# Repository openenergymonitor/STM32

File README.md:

# STM32 Energy Monitoring

The STM32 platform is a family of microcontrollers based on the Arm Cortex M processor, offering among many powerful features, plenty of 12-bit analog inputs and high speed sampling, making them particularly suitable for energy monitoring applications.

The following resources are a work in progress guide to using the STM32 platform for energy monitoring, being written as part of development work into the next generation of OpenEnergyMonitor hardware. To be included as a section in [http://learn.openenergymonitor.org](http://learn.openenergymonitor.org)

### OpenEnergyMonitor Forum threads:

- [STM32 Development thread](https://community.openenergymonitor.org/t/stm32-development)
- [STM32 Hardware Development](https://community.openenergymonitor.org/t/stm32-hardware-development/7135)
- [STM32 PlatformIO](https://community.openenergymonitor.org/t/stm32-platformio/7015)

### Getting started: STM32 (Arduino integration)

If you are familiar with the Arduino platform getting the basics working using the familiarity of the Arduino IDE and the STM32Dunio Arduino integration is a good place to start.

- [1. Blinking an LED using the NUCLEO-F303RE Development board & STM32Duino](docs/STM32Duino/Blink.md)
- [2. Basic NUCLEO-F303RE energy monitor using an EmonTxShield & EmonLib discreet sampling STM32Duino library](docs/STM32Duino/EmonLib.md)

### Introducing STM32CubeMX

ADC access using the Arduino analogRead command gives limited performance, its possible to sample much faster across many channels by using the lower level STM32 HAL (Hardware Access Layer) provided by ST. The development pathway to access these features is different and quite daunting if your primarily familiar with the Arduino platform. There is a tool called STM32CubeMX which is a kind of project builder that you can use to generate the initial outline of your project, from there you can enter your own 'user code' into the relevant placeholders in the generated project. The following set of guides give an introduction to this process:

- [1. Blink](docs/Blink.md)
- [2. Serial](docs/Serial.md)
- [3. Analog](docs/Analog.md)
- [4. DMA](docs/DMA.md)
- [5. RFM69](docs/RFM69.md)

### Hardware

Notes on hardware development and initial designs:

- [1. ST-LINK nucleo](docs/ST-LINK.md)
- [2. ST-LINK adapters](docs/st-link2.md)
- [3. Serial/UART Upload](docs/uartupload.md)
- [4. RaspberryPi UART Upload + autoreset](docs/rpiautoupload.md)

**STM32-pi_basic**

- [Eagle design 01](Hardware/stm32-pi_basic/1)
- [Prototype 1, breadboard, voltage follower & anti-alias](docs/prototype1.md)
- [STM32-pi_basic eagle design 02](Hardware/stm32-pi_basic/2)
- [STM32-pi_basic eagle design 03](Hardware/stm32-pi_basic/3)
- [STM32-pi_basic eagle design 04](Hardware/stm32-pi_basic/4)
- [Design Notes v4](docs/stm32notes.md)
- [STM32-pi_basic eagle design 05](Hardware/stm32-pi_basic/5)

**STM32-pi_full**

- [Hardware/stm32-pi_full](Hardware/stm32-pi_full)

**Misc**

- [Flashing a new chip](docs/Blink-fresh-chip.md)

### Firmware Examples

Firmware examples included in this repository:

- [1. Blink](Software/Blink)
- [2. ADC](Software/ADC)
- [3. DMA](Software/DMA)
- [4. Emon](Software/Emon): EmonTxShield Voltage and CT1 current measurement, single ADC example.
- [5. Emon1CT](Software/Emon1CT): EmonTxShield Voltage (ADC1) and CT3 current measurement (ADC2) example.
- [6. Emon1CT_ds18b20](Software/Emon1CT_ds18b20): EmonTxShield Voltage (ADC1) and CT3 current measurement (ADC2) example with DS18B20 temperature measurement.
- [7. Emon3CT](Software/Emon3CT): EmonTxShield Voltage (ADC1) and 3x CT inputs on ADC2.
- [8. Emon3CT_CB](Software/Emon3CT_CB): Firmware for [Hardware/stm32-pi_basic/5](Hardware/stm32-pi_basic/5)
- [9. Emon3CT_CB_v2](Software/Emon3CT_CB_v2): Firmware for [Hardware/stm32-pi_basic/5](Hardware/stm32-pi_basic/5) v2.
- [10. Emon3CT_RFM69](Software/Emon3CT_RFM69): EmonTxShield Voltage (ADC1), 3x CT inputs on ADC2 and RFM69 support.
- [11. Emon3CT_VET](Software/Emon3CT_VET): Basic firmware for [Hardware/stm32-pi_full](Hardware/stm32-pi_full) v2 by Trystan Lea.
- [12. emonTxshield_dBC (v13)](Software/emonTxshield_dBC): Mutli-channel energy monitor example firmware thanks to @dBC see [https://community.openenergymonitor.org/t/stm32-development/6815/232](https://community.openenergymonitor.org/t/stm32-development/6815/232)
- [13. RFM69](Software/RFM69): RFM69 library and examples.
- [14. MBUS](Software/MBUS): Example of reading data from an MBUS meter using Serial and DMA's.

**STM32 Pi Full**

- [STM32 pi v0.7 firmware basics](docs/stm32-pi.md)
- [Sombrero_VB_Blink](Software/Sombrero_VB_Blink)
- [Sombrero_VE_ADC-test](Software/Sombrero_VE_ADC-test)
- [Sombrero_VE_Blink](Software/Sombrero_VE_Blink)
- [Sombrero_VE_Working5](Sombrero_VE_Working5)

### Other:

- [STM32F103 BluePill Blink](docs/bluepill.md)
- [CAD files from ST](docs/cad-files.md)
- [CAD file of the enclosure](https://a360.co/3kcYF79)

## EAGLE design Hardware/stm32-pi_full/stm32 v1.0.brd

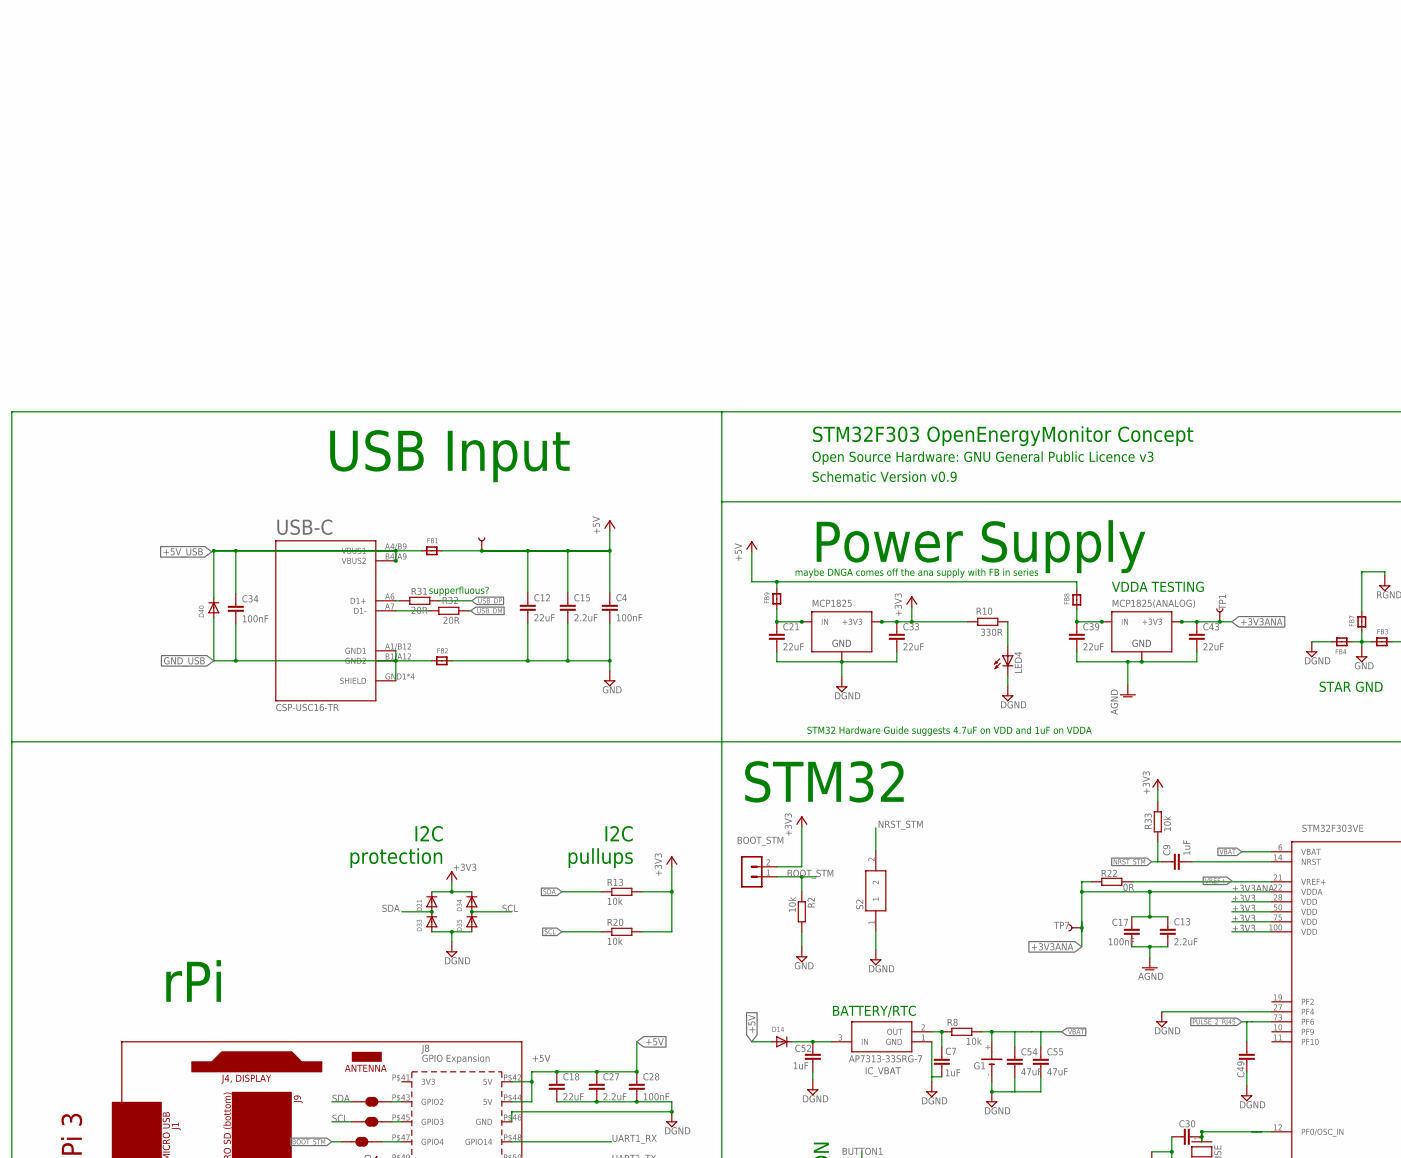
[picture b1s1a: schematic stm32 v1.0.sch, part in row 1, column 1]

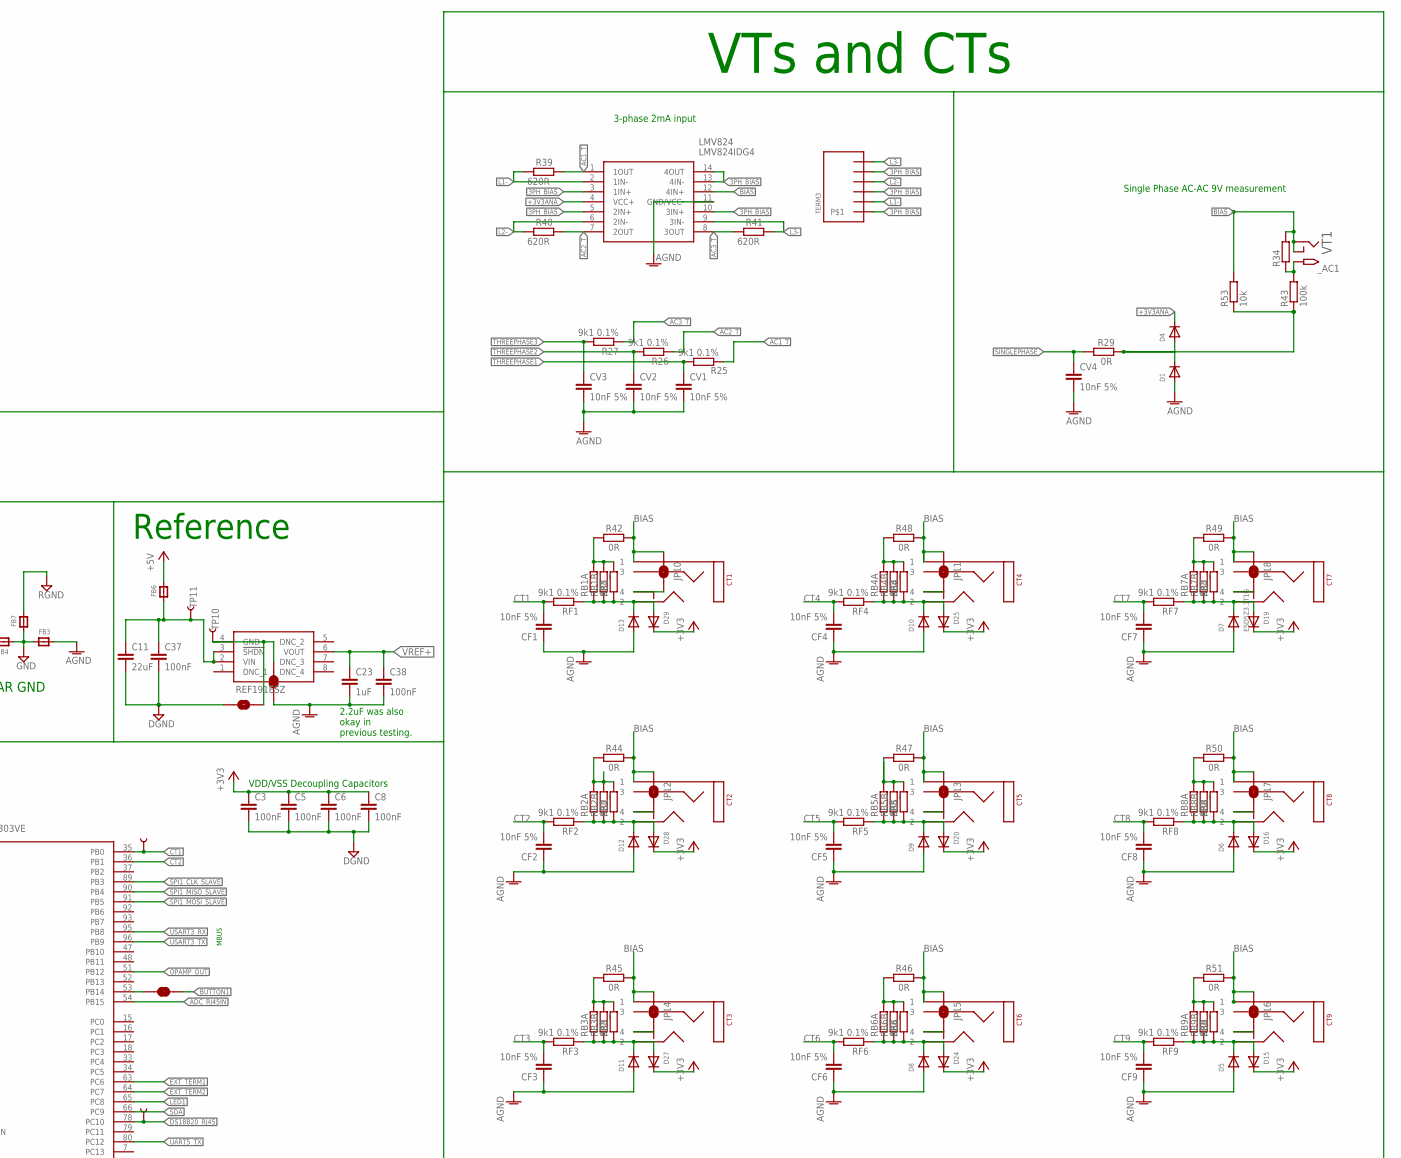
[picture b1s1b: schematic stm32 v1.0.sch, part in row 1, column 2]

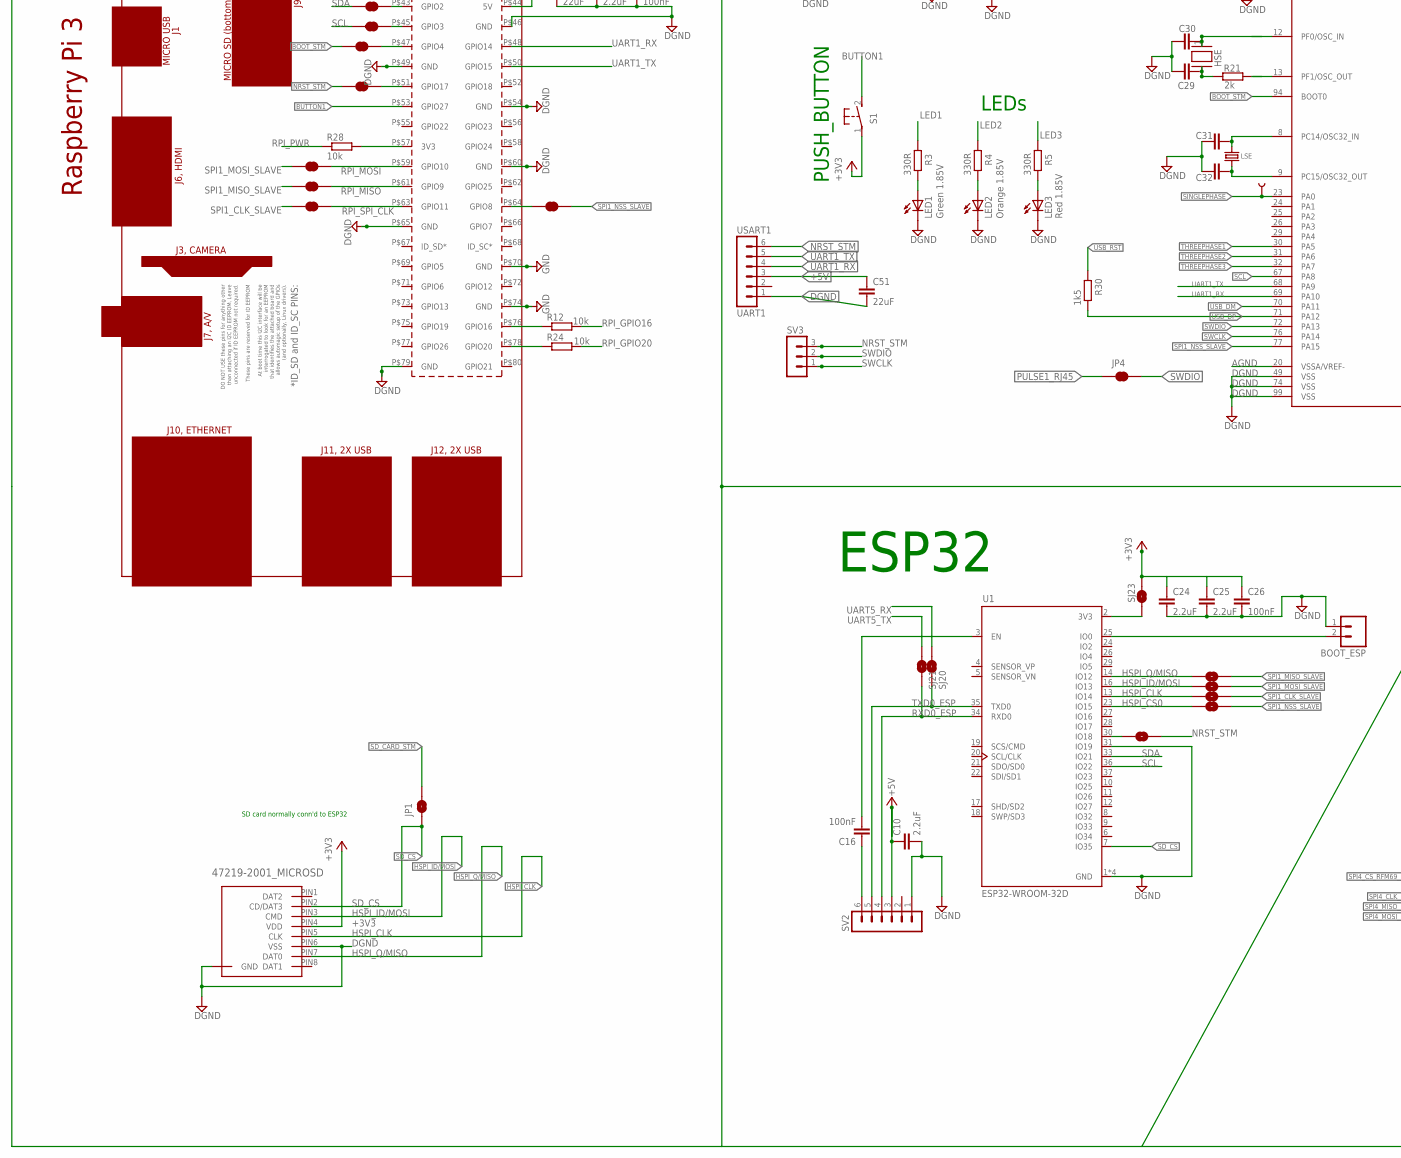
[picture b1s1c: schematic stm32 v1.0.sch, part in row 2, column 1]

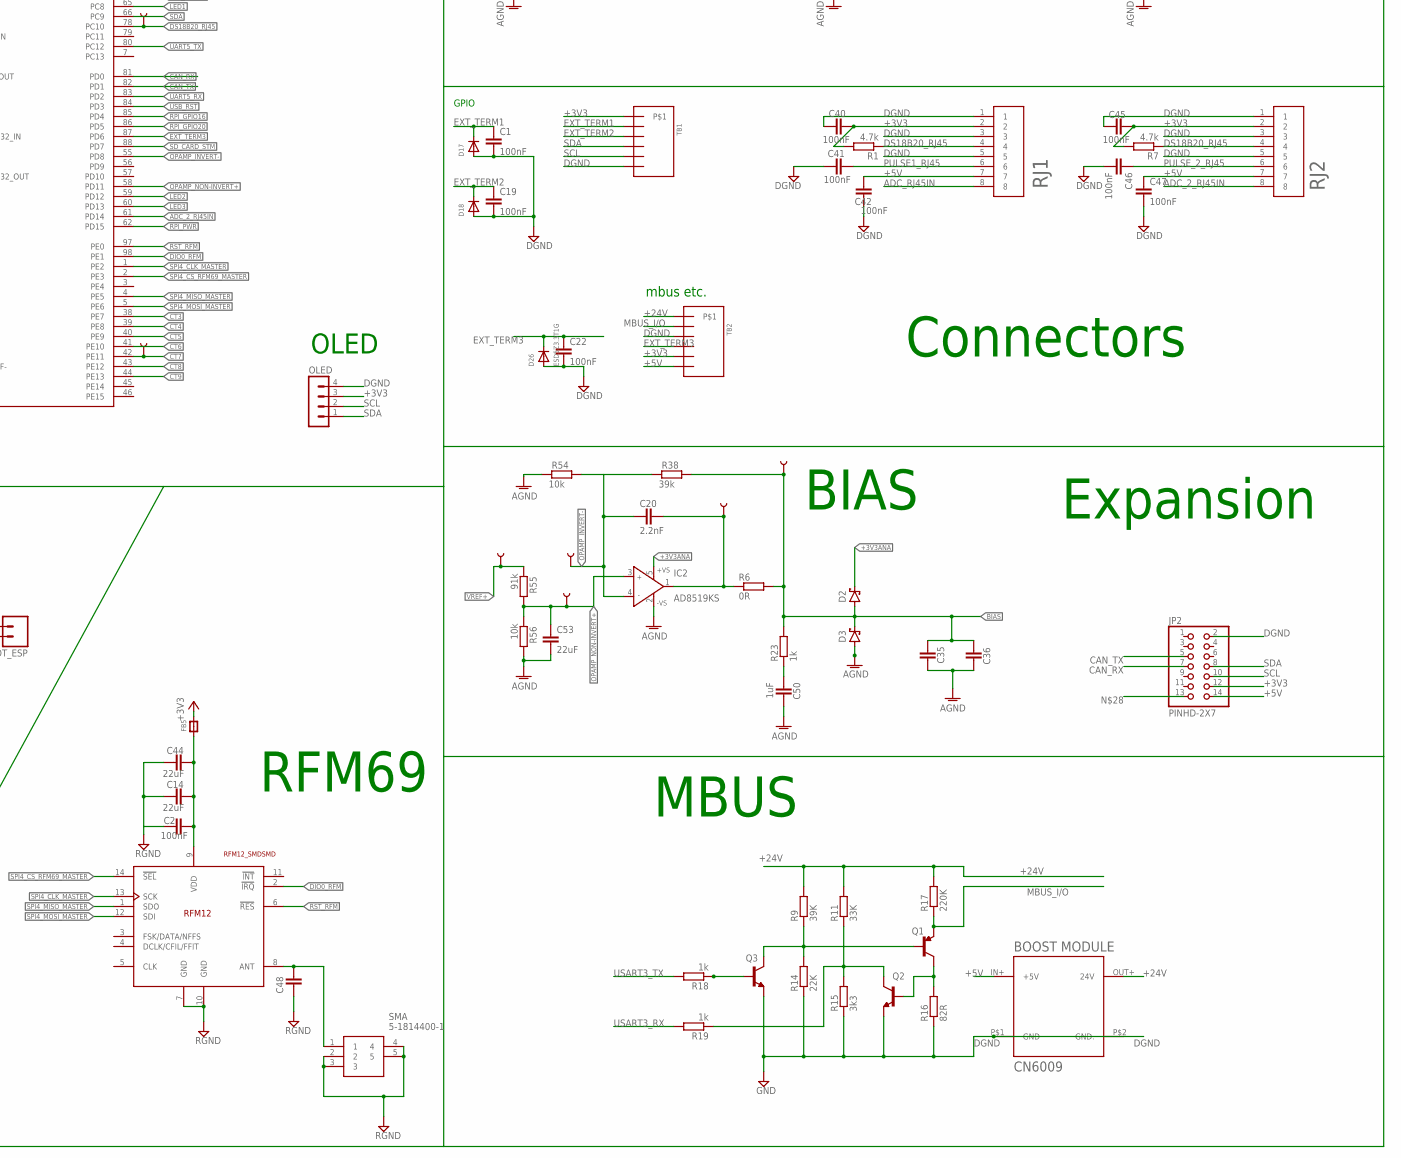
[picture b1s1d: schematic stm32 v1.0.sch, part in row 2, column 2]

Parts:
BOOT_ESP: M02PTH; 1X02
BOOT_STM: MA02-1
C1, C2, C3, C4, C5, C6, C8, C16, C17, C19, C22, C26, C28, C34, C37, C38, C40, C41, C42, C45, C46, C47, C49: 100nF; C0603
C7, C9, C23, C50, C52: 1uF; C0603
C10, C15, C24, C25, C27: 2.2uF; C0805
C11, C12, C14, C18, C21, C33, C39, C43, C44, C51, C53: 22uF; C0805
C13: 2.2uF; C0603
C20: 2.2nF; C0603
C29, C30: 15pF; C0603
C31, C32: 10pF; C0603
C35, C36, C48: C-EUC0603; C0603
C54, C55: 47uF; C0805
CF1, CF2, CF3, CF4, CF5, CF6, CF7, CF8, CF9: 10nF 5%; C0805
CT1, CT2, CT3, CT4, CT5, CT6, CT7, CT8, CT9: SJ-3523-SMT; SJ-352X-SMT; MPN SJ-3523-SMT
CV1, CV2, CV3, CV4: 10nF 5%; C0805
D1, D4, D5, D6, D7, D8, D9, D10, D11, D12, D13, D14, D15, D16, D17, D18, D19, D20, D21, D24, D25, D26, D27, D28, D29, D33, D34, D35: ESD5Z3.3T1G; SOD-523
D2, D3: SCHOTTKY_MBR0520LT1GDO-219-AB(SOD123F); SODFL3718X115; MPN MBR130LSFT1G
D40: ESD5Z5.0T1G; SOD-523
FB1, FB2: FERRITE; 0603; MPN MH1608-601Y
FB3, FB4, FB5, FB6, FB7, FB8, FB9: FERRITE_0603; _0603; MPN BLM18BD252SN1D
G1: CH291-1220LF
HSE: 6MM_3.5MM_CRYSTAL; ABMM2
IC2: AD8519KS; SC70-5
IC_VBAT: AP7313-33SRG-7; SOT96P240X135-3N
J1: JUMPER-SMT_2_NC_TRACE_NO-SILK; SMT-JUMPER_2_NC_TRACE_NO-SILK
JP1: JUMPER-SMT_2_NO_NO-SILK; SMT-JUMPER_2_NO_NO-SILK
JP2: PINHD-2X7; 2X07
JP4: JUMPER-SMT_2_NC_TRACE_NO-SILK; SMT-JUMPER_2_NC_TRACE_NO-SILK
JP10, JP11, JP12, JP13, JP14, JP15, JP16, JP17, JP18: JUMPER-SMT_2_NO_NO-SILK_ROUND; SMT-JUMPER_2_NO_NO-SILK_ROUND
LED1, LED4: Green 1.85V; CHIP-LED0805
LED2: Orange 1.85V; CHIP-LED0805
LED3: Red 1.85V; CHIP-LED0805
LMV824: LMV824IDG4; SOIC127P600X175-14N
LSE: 32.768kHz; CRYSTAL_8X3.8
MCP1825, MCP1825(ANALOG): MCP1825SOT-223-3; SOT-223
OLED: MA04-1-OLEDOLED; MA04-1-OLED
PCB2: RPI3YA; RPI3MIRROR2; MPN M20-7872042
Q1: PNP; SOT23-R; MPN SMMBT3906LT1G
Q2, Q3: NPN; SOT23-R; MPN KST3904MTF
R1, R7: 4.7k; R0603
R2, R8, R12, R13, R20, R24, R28, R33, R53, R54, R56: 10k; R0603
R3, R4, R5, R10: 330R; R0603
R6, R22, R29, R42, R44, R45, R46, R47, R48, R49, R50, R51: 0R; R0603
R9: 39K; R0603
R11: 33K; R0603
R14: 22K; R0603
R15: 3k3; R0603
R16: 82R; R0603
R17: 220K; R0603
R18, R19, R23: 1k; R0603
R21: 2k; R0603
R25, R26, R27: 9k1 0.1%; R0603
R30: 1k5; R0603
R31, R32: 20R; R0603
R34: R-EU_R1210; R1210
R38: 39k; R0603
R39, R40, R41: 620R; R0603
R43: 100k; R0603
R55: 91k; R0603
RB1A, RB2A, RB3A, RB4A, RB5A, RB6A, RB7A, RB8A, RB9A: 6R8; R0805
RB1B, RB2B, RB3B, RB4B, RB5B, RB6B, RB7B, RB8B, RB9B: R-EU_R0805; R0805
RB1_, RB2_, RB3_, RB4_, RB5_, RB6_, RB7_, RB8_, RB9_: R-EU_0207/10; 0207/10
REF19X: REF191ESZ; SOIC127P599X175-8N; MPN REF191ESZ
RF1, RF2, RF3, RF4, RF5, RF6, RF7, RF8, RF9: 9k1 0.1%; R0603
RFM69HCW: RFM12_SMDSMD; RFM12
RJ1, RJ2: 95501-6889; 955016889
S1: 31-XX; B3F-31XX
S2: KSS221GLFS; KSS
SJ1, SJ3, SJ5, SJ6, SJ7, SJ14, SJ26, SJ27, SJ32: JUMPER-SMT_2_NC_TRACE_NO-SILK; SMT-JUMPER_2_NC_TRACE_NO-SILK
SJ2, SJ4, SJ9, SJ10, SJ13: JUMPER-SMT_2_NO_SILK; SMT-JUMPER_2_NO_SILK
SJ20, SJ21, SJ23, SJ25: SOLDERJUMPERNO; SJ_2S-NO
SMA: 5-1814400-1; 518144001
STM32F303VE: STM32F303VE; TQFP100
SV2: MA06-1
SV3: MA03-1
TB1, TB2: 3.5MM_TB_X6; 3.5MM_X6
TERM3: 3.5MM_TB_X6; 3.5MM_X6
TP1, TP2, TP3, TP4, TP5, TP6, TP7, TP8, TP9, TP10, TP11, TP18, TP19, TP20: TEST-POINTPOGO_PTH; 1X01_NO_SILK
U1: ESP32-WROOM-32D; MODULE_ESP32-WROOM-32D
U$2: BOOST_MODULE; BOOST
U$7: 47219-2001_MICROSD
USART1: UART1; MA06-1
USB-C: CSP-USC16-TR; USB-C
VT1: ADC-028-2-T; DCJACK_2MM_SMT; MPN ADC-028-1-T

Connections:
3PH_BIAS: LMV824.3 (1IN+), LMV824.5 (2IN+), LMV824.10 (3IN+), LMV824.13 (4IN-), LMV824.14 (4OUT), TERM3.P$1, TERM3.P$3, TERM3.P$5
+3V3: BOOT_STM.2, C3.1, C5.1, C6.1, C8.1, C24.1, C25.1, C26.1, C33.1, C40.1, C45.1, D21.K (C), D34.K (C), FB5.2, JP2.12, MCP1825.3 (+3V3), OLED.3, R1.2, R7.2, R10.2, R13.2, R20.2, R33.1, RJ1.2, RJ2.2, S1.1, SJ23.2, STM32F303VE.28 (VDD), STM32F303VE.50 (VDD), STM32F303VE.75 (VDD), STM32F303VE.100 (VDD), TB1.P$1, TB2.P$5, U$7.PIN4 (VDD)
+3V3ANA: C13.1, C17.1, C43.1, D2.1 (C), D4.K (C), D15.K (C), D16.K (C), D19.K (C), D20.K (C), D24.K (C), D25.K (C), D27.K (C), D28.K (C), D29.K (C), IC2.5 (+VS), LMV824.4 (VCC+), MCP1825(ANALOG).3 (+3V3), R22.1, STM32F303VE.22 (VDDA), TP1.1, TP7.1
+5V: C4.1, C10.1, C12.1, C15.1, C18.1, C27.1, C28.1, C42.1, C47.1, C51.1, D14.A, FB1.2, FB6.2, FB8.2, FB9.2, JP2.14, PCB2.P$42 (5V), PCB2.P$44 (5V), RJ1.7, RJ2.7, SV2.3, TB2.P$6, TP4.1, U$2.IN+ (+5V), USART1.3
+5V_A: C39.1, FB8.1, MCP1825(ANALOG).1 (IN)
+5V_BATT: C52.1, D14.K (C), IC_VBAT.3 (IN)
+5V_D: C21.1, FB9.1, MCP1825.1 (IN)
+5V_REF: C11.1, C37.1, FB6.1, REF19X.2 (VIN), REF19X.3 (!SHDN), TP11.1
+5V_USB: C34.1, D40.K (C), FB1.1, USB-C.A4/B9 (VBUS1), USB-C.B4/A9 (VBUS2)
+24V: R9.2, R11.2, R17.2, TB2.P$1, U$2.OUT+ (24V)
AC1: D1.K (C), D4.A, R29.1, R43.1, R53.1
AC1_T: LMV824.1 (1OUT), R25.1, R39.1
AC2_T: LMV824.7 (2OUT), R26.1, R40.1
AC3_T: LMV824.8 (3OUT), R27.1, R41.2
ADC_2_RJ45IN: RJ2.8, STM32F303VE.61 (PD14)
ADC_RJ45IN: RJ1.8, STM32F303VE.54 (PB15)
AGND: C13.2, C17.2, C23.2, C35.2, C36.2, C38.2, C39.2, C43.2, C50.2, C53.2, CF1.1, CF2.1, CF3.1, CF4.1, CF5.1, CF6.1, CF7.1, CF8.1, CF9.1, CV1.2, CV2.2, CV3.2, CV4.2, D1.A, D3.2 (A), D5.A, D6.A, D7.A, D8.A, D9.A, D10.A, D11.A, D12.A, D13.A, FB3.2, IC2.2 (-VS), LMV824.11 (GND/VCC-), MCP1825(ANALOG).2 (GND), MCP1825(ANALOG).4 (GND), R54.2, R56.1, SJ1.1, STM32F303VE.20 (VSSA/VREF-)
ANT: C48.1, RFM69HCW.8 (ANT), SMA.1
BIAS: C35.1, C36.1, CT1.P$1 (1), CT2.P$1 (1), CT3.P$1 (1), CT4.P$1 (1), CT5.P$1 (1), CT6.P$1 (1), CT7.P$1 (1), CT8.P$1 (1), CT9.P$1 (1), D2.2 (A), D3.1 (C), JP10.1, JP11.1, JP12.1, JP13.1, JP14.1, JP15.1, JP16.1, JP17.1, JP18.1, LMV824.12 (4IN+), R6.2, R23.2, R34.2, R38.1, R42.1, R44.1, R45.1, R46.1, R47.1, R48.1, R49.1, R50.1, R51.1, R53.2, TP3.1, VT1.GND (RING), VT1.GNDBREAK (RING_SW)
BOOT0_RPI: J1.2, PCB2.P$47 (GPIO4)
BOOT_STM: BOOT_STM.1, J1.1, R2.1, STM32F303VE.94 (BOOT0)
BUTTON1: PCB2.P$53 (GPIO27), S1.2 (S), SJ3.1
BUTTON1_STM: SJ3.2, STM32F303VE.53 (PB14)
CAN_RX: JP2.7, STM32F303VE.81 (PD0)
CAN_TX: JP2.5, STM32F303VE.82 (PD1)
CT1: CF1.2, RF1.2, STM32F303VE.35 (PB0), TP18.1
CT2: CF2.2, RF2.2, STM32F303VE.36 (PB1)
CT3: CF3.2, RF3.2, STM32F303VE.38 (PE7)
CT4: CF4.2, RF4.2, STM32F303VE.39 (PE8)
CT5: CF5.2, RF5.2, STM32F303VE.40 (PE9)
CT6: CF6.2, RF6.2, STM32F303VE.41 (PE10)
CT7: CF7.2, RF7.2, STM32F303VE.42 (PE11), TP19.1
CT8: CF8.2, RF8.2, STM32F303VE.43 (PE12)
CT9: CF9.2, RF9.2, STM32F303VE.44 (PE13)
CT_IN1: CT1.P$2 (2), D13.K (C), D29.A, RB1A.1, RB1B.1, RB1_.1, RF1.1
CT_IN2: CT2.P$2 (2), D12.K (C), D28.A, RB2A.1, RB2B.1, RB2_.1, RF2.1
CT_IN3: CT3.P$2 (2), D11.K (C), D27.A, RB3A.1, RB3B.1, RB3_.1, RF3.1
CT_IN4: CT4.P$2 (2), D10.K (C), D25.A, RB4A.1, RB4B.1, RB4_.1, RF4.1
CT_IN5: CT5.P$2 (2), D9.K (C), D20.A, RB5A.1, RB5B.1, RB5_.1, RF5.1
CT_IN6: CT6.P$2 (2), D8.K (C), D24.A, RB6A.1, RB6B.1, RB6_.1, RF6.1
CT_IN7: CT7.P$2 (2), D7.K (C), D19.A, RB7A.1, RB7B.1, RB7_.1, RF7.1
CT_IN8: CT8.P$2 (2), D6.K (C), D16.A, RB8A.1, RB8B.1, RB8_.1, RF8.1
CT_IN9: CT9.P$2 (2), D5.K (C), D15.A, RB9A.1, RB9B.1, RB9_.1, RF9.1
DGND: BOOT_ESP.1, C1.2, C3.2, C5.2, C6.2, C7.2, C8.2, C10.2, C11.2, C18.2, C19.2, C21.2, C22.2, C24.2, C25.2, C26.2, C27.2, C28.2, C29.2, C30.2, C31.2, C32.2, C33.2, C37.2, C40.2, C41.2, C42.2, C45.2, C46.2, C47.2, C49.2, C51.2, C52.2, C54.2, C55.2, D17.A, D18.A, D26.A, D33.A, D35.A, FB4.2, G1.-, IC_VBAT.1 (GND), JP2.2, LED1.C, LED2.C, LED3.C, LED4.C, MCP1825.2 (GND), MCP1825.4 (GND), OLED.4, PCB2.P$46 (GND), PCB2.P$49 (GND), PCB2.P$54 (GND), PCB2.P$60 (GND), PCB2.P$65 (GND), PCB2.P$70 (GND), PCB2.P$74 (GND), PCB2.P$79 (GND), Q2.2 (E), Q3.2 (E), R2.2, R14.1, R15.1, R16.1, RJ1.1, RJ1.3, RJ1.5, RJ2.1, RJ2.3, RJ2.5, S2.1, SJ2.1, STM32F303VE.27 (PF4), STM32F303VE.49 (VSS), STM32F303VE.74 (VSS), STM32F303VE.99 (VSS), SV2.1, TB1.P$6, TB2.P$3, U1.1 (GND), U1.15 (GND), U1.31 (IO19), U1.38 (GND), U1.39 (GND), U$2.P$1 (GND), U$2.P$2 (GND.), U$7.P$1 (GND), U$7.P$2 (GND), U$7.P$3 (GND), U$7.P$4 (GND), U$7.PIN6 (VSS), USART1.1
DIO0_RFM: RFM69HCW.2 (!IRQ), STM32F303VE.98 (PE1)
DS18B20_RJ45: R1.1, R7.1, RJ1.4, RJ2.4, STM32F303VE.78 (PC10), TP9.1
ESP_PWR_PRE: SJ23.1, U1.2 (3V3)
EXT_TERM1: C1.1, D17.K (C), STM32F303VE.63 (PC6), TB1.P$2
EXT_TERM2: C19.1, D18.K (C), STM32F303VE.64 (PC7), TB1.P$3
EXT_TERM3: C22.1, D26.K (C), STM32F303VE.87 (PD6), TB2.P$4
GND: C4.2, C12.2, C15.2, FB2.2, FB3.1, FB4.1, FB7.1
GND_USB: C34.2, D40.A, FB2.1, USB-C.A1/B12 (GND1), USB-C.B1/A12 (GND2), USB-C.GND1 (SHIELD), USB-C.GND2 (SHIELD), USB-C.GND3 (SHIELD), USB-C.GND4 (SHIELD)
HSE_IN: C30.1, HSE.1 (CRYSTAL_1), STM32F303VE.12 (PF0/OSC_IN)
HSE_OUT: R21.1, STM32F303VE.13 (PF1/OSC_OUT)
HSE_OUT_: C29.1, HSE.3 (CRYSTAL_2), R21.2
HSPI_CLK: SJ10.1, U1.13 (IO14), U$7.PIN5 (CLK)
HSPI_CS0: SJ13.1, U1.23 (IO15)
HSPI_ID/MOSI: SJ9.1, U1.16 (IO13), U$7.PIN3 (CMD)
HSPI_Q/MISO: SJ4.1, U1.14 (IO12), U$7.PIN7 (DAT0)
L1-: LMV824.2 (1IN-), R39.2, TERM3.P$2
L2-: LMV824.6 (2IN-), R40.2, TERM3.P$4
L3-: LMV824.9 (3IN-), R41.1, TERM3.P$6
LED1: R3.2, STM32F303VE.65 (PC8)
LED2: R4.2, STM32F303VE.59 (PD12)
LED3: R5.2, STM32F303VE.60 (PD13)
MBUS_I/O: Q1.2 (E), R17.1, TB2.P$2
unnamed: CT1.P$4 (4), JP10.2
unnamed: CT4.P$4 (4), JP11.2
unnamed: LED2.A, R4.1
unnamed: LED3.A, R5.1
unnamed: C50.1, R23.1
unnamed: CT2.P$4 (4), JP12.2
unnamed: LED4.A, R10.1
unnamed: CT5.P$4 (4), JP13.2
unnamed: PCB2.P$64 (GPIO8), SJ14.1
unnamed: REF19X.4 (GND), SJ1.2, SJ2.2, TP10.1
unnamed: CT3.P$4 (4), JP14.2
unnamed: C16.1, SV2.6
unnamed: C16.2, U1.3 (EN)
unnamed: C7.1, IC_VBAT.2 (OUT), R8.1
unnamed: BOOT_ESP.2, U1.25 (IO0)
unnamed: PCB2.P$57 (3V3), R28.2
unnamed: CT6.P$4 (4), JP15.2
unnamed: CT9.P$4 (4), JP16.2
unnamed: CT8.P$4 (4), JP17.2
unnamed: CT7.P$4 (4), JP18.2
unnamed: R47.2, RB5A.2, RB5B.2, RB5_.2
unnamed: R46.2, RB6A.2, RB6B.2, RB6_.2
unnamed: R42.2, RB1A.2, RB1B.2, RB1_.2
unnamed: R44.2, RB2A.2, RB2B.2, RB2_.2
unnamed: R50.2, RB8A.2, RB8B.2, RB8_.2
unnamed: Q1.3 (C), Q2.1 (B), R16.2
unnamed: Q1.1 (B), Q3.3 (C), R9.1, R14.2
unnamed: Q2.3 (C), R11.1, R15.2, R19.1
unnamed: Q3.1 (B), R18.1
unnamed: R51.2, RB9A.2, RB9B.2, RB9_.2
unnamed: R48.2, RB4A.2, RB4B.2, RB4_.2
unnamed: R49.2, RB7A.2, RB7B.2, RB7_.2
unnamed: R45.2, RB3A.2, RB3B.2, RB3_.2
unnamed: LED1.A, R3.1
NRST_STM: C9.1, R33.2, S2.2, SJ25.2, SJ32.1, SV3.3, USART1.6
NRST_STM_: C9.2, STM32F303VE.14 (NRST)
NRST_STM_ESP: SJ25.1, U1.30 (IO18)
NRST_STM_RPI: PCB2.P$51 (GPIO17), SJ32.2
OPAMP_INVERT-: C20.1, IC2.4 (IN-), R38.2, R54.1, STM32F303VE.55 (PD8), TP6.1
OPAMP_NON-INVERT+: C53.1, IC2.3 (IN+), R55.1, R56.2, STM32F303VE.58 (PD11), TP2.1
OPAMP_OUT: C20.2, IC2.1 (OUT), R6.1, STM32F303VE.51 (PB12), TP5.1
PC14: C31.1, LSE.P$1 (1), STM32F303VE.8 (PC14/OSC32_IN)
PC15: C32.1, LSE.P$4 (2), STM32F303VE.9 (PC15/OSC32_OUT)
PULSE1_RJ45: C41.1, JP4.1, RJ1.6
PULSE_2_RJ45: C46.1, C49.1, RJ2.6, STM32F303VE.73 (PF6)
RGND: C2.2, C14.2, C44.2, C48.2, FB7.2, RFM69HCW.7 (GND), RFM69HCW.10 (GND), SMA.2, SMA.3, SMA.4, SMA.5
RPI_GPIO16: R12.2, STM32F303VE.85 (PD4)
RPI_GPIO16_RPI: PCB2.P$76 (GPIO16), R12.1
RPI_GPIO20: R24.2, STM32F303VE.86 (PD5)
RPI_GPIO20_RPI: PCB2.P$78 (GPIO20), R24.1
RPI_MISO: PCB2.P$61 (GPIO9), SJ6.2
RPI_MOSI: PCB2.P$59 (GPIO10), SJ5.2
RPI_PWR: R28.1, STM32F303VE.62 (PD15)
RPI_SPI_CLK: PCB2.P$63 (GPIO11), SJ7.2
RST_RFM: RFM69HCW.6 (!RES), STM32F303VE.97 (PE0)
RXD0_ESP: SJ21.2, SV2.4, U1.34 (RXD0)
SCL: D34.A, D35.K (C), JP2.10, OLED.2, R20.1, SJ27.2, STM32F303VE.67 (PA8), TB1.P$5, U1.36 (IO22)
SCL_: PCB2.P$45 (GPIO3), SJ27.1
SDA: D21.A, D33.K (C), JP2.8, OLED.1, R13.1, SJ26.1, STM32F303VE.66 (PC9), TB1.P$4, U1.33 (IO21)
SDA_: PCB2.P$43 (GPIO2), SJ26.2
SD_CARD_STM: JP1.2, STM32F303VE.88 (PD7)
SD_CS: JP1.1, U1.7 (IO35), U$7.PIN2 (CD/DAT3)
SINGLEPHASE: CV4.1, R29.2, STM32F303VE.23 (PA0), TP20.1
SPI1_CLK_SLAVE: SJ7.1, SJ10.2, STM32F303VE.89 (PB3)
SPI1_MISO_SLAVE: SJ4.2, SJ6.1, STM32F303VE.90 (PB4)
SPI1_MOSI_SLAVE: SJ5.1, SJ9.2, STM32F303VE.91 (PB5)
SPI1_NSS_SLAVE: SJ13.2, SJ14.2, STM32F303VE.77 (PA15)
SPI4_CLK_MASTER: RFM69HCW.13 (SCK), STM32F303VE.1 (PE2)
SPI4_CS_RFM69_MASTER: RFM69HCW.14 (!SEL), STM32F303VE.2 (PE3)
SPI4_MISO_MASTER: RFM69HCW.1 (SDO), STM32F303VE.4 (PE5)
SPI4_MOSI_MASTER: RFM69HCW.12 (SDI), STM32F303VE.5 (PE6)
SWCLK: STM32F303VE.76 (PA14), SV3.1
SWDIO: JP4.2, STM32F303VE.72 (PA13), SV3.2
THREEPHASE1: CV1.1, R25.2, STM32F303VE.30 (PA5)
THREEPHASE2: CV2.1, R26.2, STM32F303VE.31 (PA6)
THREEPHASE3: CV3.1, R27.2, STM32F303VE.32 (PA7)
TXD0_ESP: SJ20.2, SV2.5, U1.35 (TXD0)
UART1_RX: PCB2.P$48 (GPIO14), STM32F303VE.69 (PA10), USART1.4
UART1_TX: PCB2.P$50 (GPIO15), STM32F303VE.68 (PA9), USART1.5
UART5_RX: SJ20.1, STM32F303VE.83 (PD2)
UART5_TX: SJ21.1, STM32F303VE.80 (PC12)
USART3_RX: R19.2, STM32F303VE.95 (PB8)
USART3_TX: R18.2, STM32F303VE.96 (PB9)
USB_DM: R32.2, STM32F303VE.70 (PA11)
USB_DM_: R32.1, USB-C.A7 (D1-)
USB_DP: R30.1, R31.2, STM32F303VE.71 (PA12)
USB_DP_: R31.1, USB-C.A6 (D1+)
USB_RST: R30.2, STM32F303VE.84 (PD3)
VBAT: C54.1, C55.1, G1.+, R8.2, STM32F303VE.6 (VBAT)
VDD: C2.1, C14.1, C44.1, FB5.1, RFM69HCW.9 (VDD)
VREF+: C23.1, C38.1, R22.2, R55.2, REF19X.6 (VOUT), STM32F303VE.21 (VREF+), TP8.1
_AC1: R34.1, R43.2, VT1.PWR2 (TIP)

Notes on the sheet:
VDD/VSS Decoupling Capacitors
Single Phase AC-AC 9V measurement
VTs and CTs
STM32F303 OpenEnergyMonitor Concept
Power Supply
STM32
Open Source Hardware: GNU General Public Licence v3
Reference
ESP32
MBUS
rPi
RFM69
Connectors
Expansion
LEDs
PUSH_BUTTON
OLED
USB Input
BATTERY/RTC
I2C pullups
SD card normally conn'd to ESP32
VDDA TESTING
Schematic Version v0.9
STAR GND
STM32 Hardware Guide suggests 4.7uF on VDD and 1uF on VDDA
supperfluous?
maybe DNGA comes off the ana supply with FB in series
2.2uF was also okay in previous testing.
I2C protection
GPIO
mbus etc.
3-phase 2mA input
BIAS

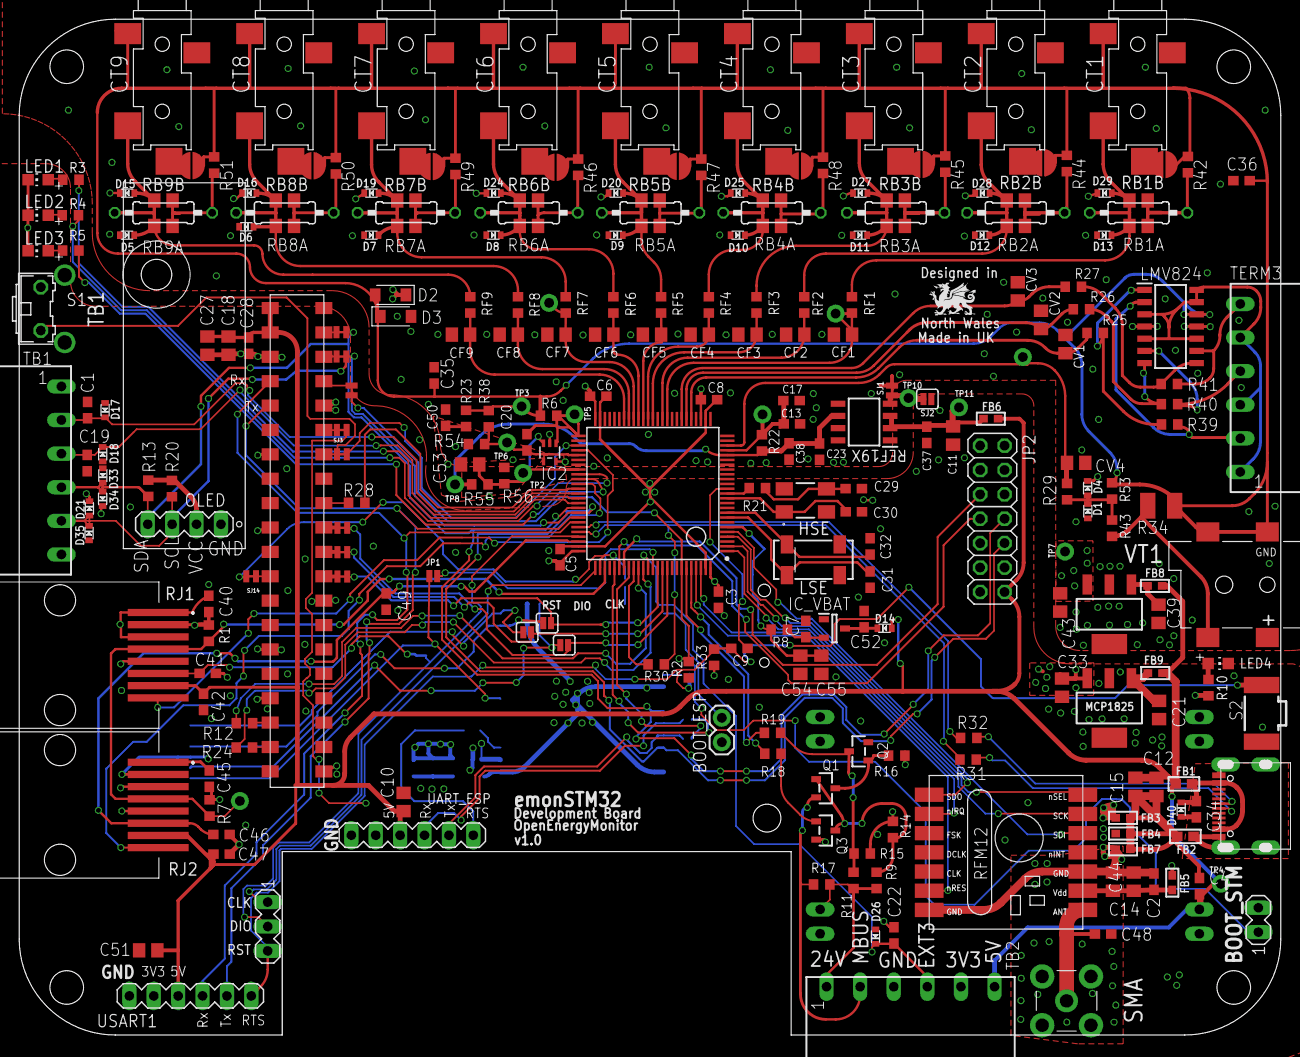
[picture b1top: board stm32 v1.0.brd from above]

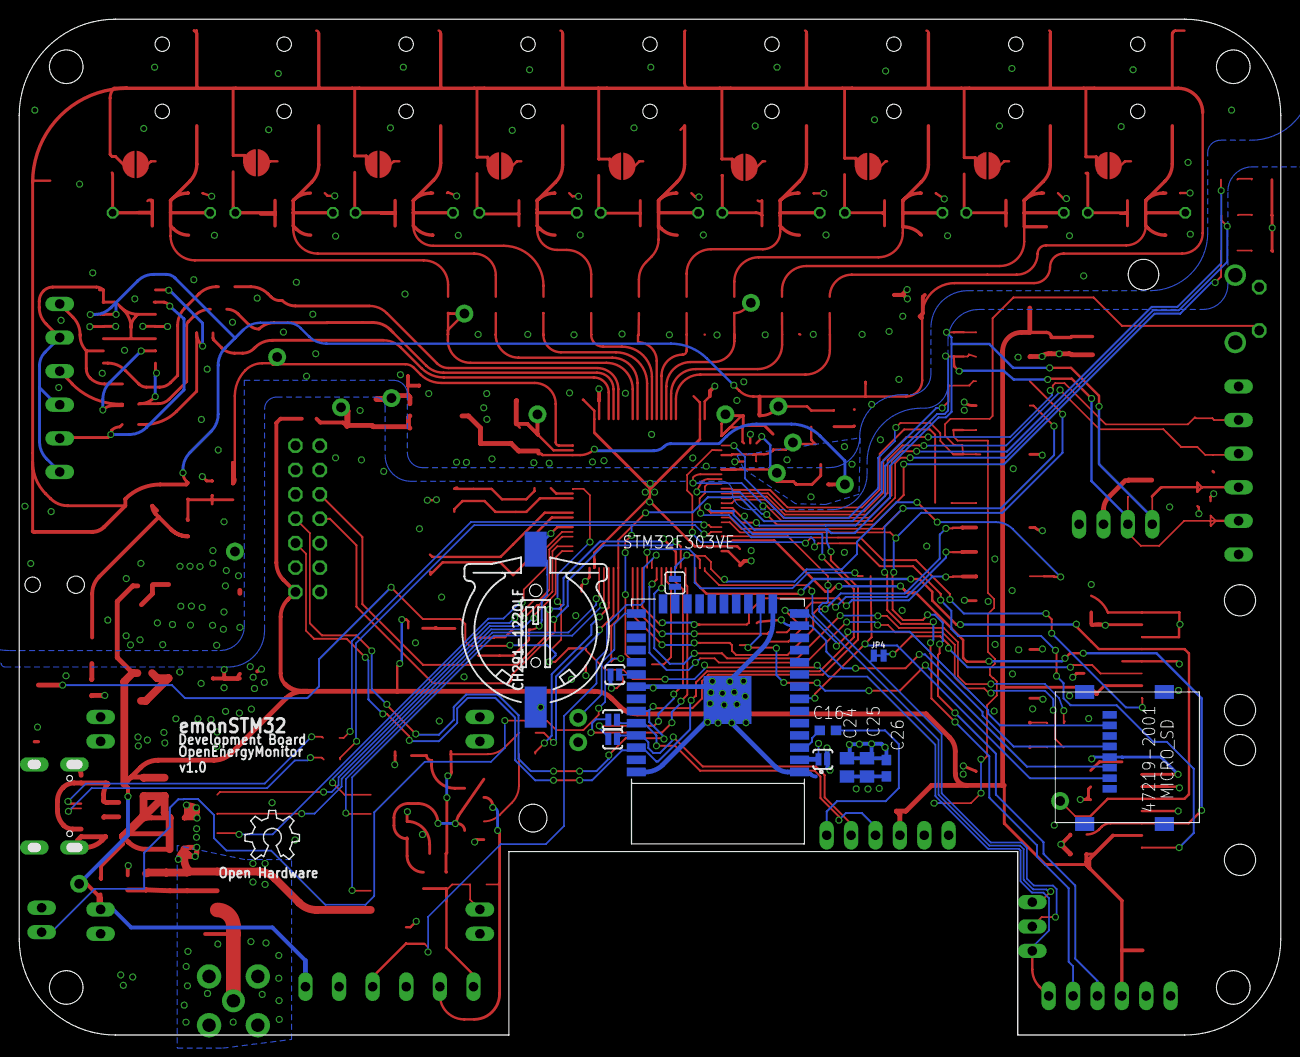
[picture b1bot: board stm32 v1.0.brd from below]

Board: 4 copper layers, 131.4 x 105.8 mm, 289 parts (14 on the bottom side), 158 nets.

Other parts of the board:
LOGO1: OSHW_LOGO_6MILX0200-NT; OSHW_6X200_NOTEXT

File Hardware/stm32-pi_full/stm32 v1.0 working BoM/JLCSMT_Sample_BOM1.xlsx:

Comment | Designator | Footprint
100nF | C1 | C0603
2.2uF | C10 | C0805
22uF | C11 | C0805
22uF | C12 | C0805
2.2uF | C13 | C0603
22uF | C14 | C0805
2.2uF | C15 | C0805
100nF | C17 | C0603
22uF | C18 | C0805
100nF | C19 | C0603
100nF | C2 | C0603
2.2nF | C20 | C0603
22uF | C21 | C0805
100nF | C22 | C0603
1uF | C23 | C0603
2.2uF | C27 | C0805
100nF | C28 | C0603
15pF | C29 | C0603
100nF | C3 | C0603
15pF | C30 | C0603
10pF | C31 | C0603
10pF | C32 | C0603
22uF | C33 | C0805
100nF | C34 | C0603
100nF | C37 | C0603
100nF | C38 | C0603
22uF | C39 | C0805
100nF | C4 | C0603
100nF | C40 | C0603
100nF | C41 | C0603
100nF | C42 | C0603
22uF | C43 | C0805
22uF | C44 | C0805
100nF | C45 | C0603
100nF | C46 | C0603
100nF | C47 | C0603
100nF | C49 | C0603
100nF | C5 | C0603
1uF | C50 | C0603
22uF | C51 | C0805
1uF | C52 | C0603
22uF | C53 | C0805
47uF | C54 | C0805
47uF | C55 | C0805
100nF | C6 | C0603
1uF | C7 | C0603
100nF | C8 | C0603
1uF | C9 | C0603
10nF 5% | CF1 | C0805
10nF 5% | CF2 | C0805
10nF 5% | CF3 | C0805
10nF 5% | CF4 | C0805
10nF 5% | CF5 | C0805
10nF 5% | CF6 | C0805
10nF 5% | CF7 | C0805
10nF 5% | CF8 | C0805
10nF 5% | CF9 | C0805
10nF 5% | CV1 | C0805
10nF 5% | CV2 | C0805
10nF 5% | CV3 | C0805
10nF 5% | CV4 | C0805
ESD5Z3.3T1G | D1 | SOD-523
SCHOTTKY_MBR0520LT1GDO-219-AB(SOD123F) | D2 | SODFL3718X115
SCHOTTKY_MBR0520LT1GDO-219-AB(SOD123F) | D3 | SODFL3718X115
ESD5Z3.3T1G | D4 | SOD-523
ESD5Z3.3T1G | D5 | SOD-523
ESD5Z3.3T1G | D6 | SOD-523
ESD5Z3.3T1G | D7 | SOD-523
ESD5Z3.3T1G | D8 | SOD-523
ESD5Z3.3T1G | D9 | SOD-523
ESD5Z3.3T1G | D10 | SOD-523
ESD5Z3.3T1G | D11 | SOD-523
ESD5Z3.3T1G | D12 | SOD-523
ESD5Z3.3T1G | D13 | SOD-523
ESD5Z3.3T1G | D14 | SOD-523
ESD5Z3.3T1G | D15 | SOD-523
ESD5Z3.3T1G | D16 | SOD-523
ESD5Z3.3T1G | D17 | SOD-523
ESD5Z3.3T1G | D18 | SOD-523
ESD5Z3.3T1G | D19 | SOD-523
ESD5Z3.3T1G | D20 | SOD-523
ESD5Z3.3T1G | D21 | SOD-523
ESD5Z3.3T1G | D24 | SOD-523
ESD5Z3.3T1G | D25 | SOD-523
ESD5Z3.3T1G | D26 | SOD-523
ESD5Z3.3T1G | D27 | SOD-523
ESD5Z3.3T1G | D28 | SOD-523
ESD5Z3.3T1G | D29 | SOD-523
ESD5Z3.3T1G | D33 | SOD-523
ESD5Z3.3T1G | D34 | SOD-523
ESD5Z3.3T1G | D35 | SOD-523
ESD5Z5.0T1G | D40 | SOD-523
ferrite | FB1 | R0603
ferrite | FB2 | R0603
ferrite | FB3 | R0603
ferrite | FB4 | R0603
ferrite | FB5 | R0603
ferrite | FB6 | R0603
ferrite | FB7 | R0603
ferrite | FB8 | R0603
ferrite | FB9 | R0603
AP7313-33SRG-7 | IC_VBAT | SOT96P240X135-3N
white led 0805 C34499 | LED1 | LED 0805
yellow led 0805 C2296 | LED2 | LED 0805
red led 0805 C84256 | LED3 | LED 0805
white led 0805 C34499 | LED4 | LED 0805
LMV824IDG4 | LMV824 | SOIC127P600X175-14N
MCP1825SOT-223-3 | MCP1825 | SOT-223
MCP1825SOT-223-3 | MCP1825(ANALOG) | SOT-223
pnp | Q1 | SOT23-R
npn | Q2 | SOT23-R
npn | Q3 | SOT23-R
4.7k | R1 | R0603
330R | R10 | R0603
33K | R11 | R0603
10k | R12 | R0603
10k | R13 | R0603
22K | R14 | R0603
3k3 | R15 | R0603
82R | R16 | R0603
220K | R17 | R0603
1k | R18 | R0603
1k | R19 | R0603
10k | R2 | R0603
10k | R20 | R0603
2k | R21 | R0603
0R | R22 | R0603
1k | R23 | R0603
10k | R24 | R0603
9k1 0.1% | R25 | R0603
9k1 0.1% | R26 | R0603
9k1 0.1% | R27 | R0603
10k | R28 | R0603
0R | R29 | R0603
330R | R3 | R0603
1k5 | R30 | R0603
20R | R31 | R0603
20R | R32 | R0603
10k | R33 | R0603
39k | R38 | R0603
620R | R39 | R0603
330R | R4 | R0603
620R | R40 | R0603
620R | R41 | R0603
0R | R42 | R0603
100k | R43 | R0603
0R | R44 | R0603
0R | R45 | R0603
0R | R46 | R0603
0R | R47 | R0603
0R | R48 | R0603
0R | R49 | R0603
330R | R5 | R0603
0R | R50 | R0603
0R | R51 | R0603
10k | R53 | R0603
10k | R54 | R0603
91k | R55 | R0603
10k | R56 | R0603
0R | R6 | R0603
4.7k | R7 | R0603
10k | R8 | R0603
39K | R9 | R0603
6R8 | RB1A | R0805
6R8 | RB2A | R0805
6R8 | RB3A | R0805
6R8 | RB4A | R0805
6R8 | RB5A | R0805
6R8 | RB6A | R0805
6R8 | RB7A | R0805
6R8 | RB8A | R0805
6R8 | RB9A | R0805
9k1 0.1% | RF1 | R0603
9k1 0.1% | RF2 | R0603
9k1 0.1% | RF3 | R0603
9k1 0.1% | RF4 | R0603
9k1 0.1% | RF5 | R0603
9k1 0.1% | RF6 | R0603
9k1 0.1% | RF7 | R0603
9k1 0.1% | RF8 | R0603
9k1 0.1% | RF9 | R0603

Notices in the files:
parts and their libraries:
SparkFun-Connectors: Licensing: Creative Commons ShareAlike 4.0 International - https://creativecommons.org/licenses/by-sa/4.0
microbuilder: This work is placed in the public domain, and may be freely used for commercial and non-commercial work with the following conditions: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
